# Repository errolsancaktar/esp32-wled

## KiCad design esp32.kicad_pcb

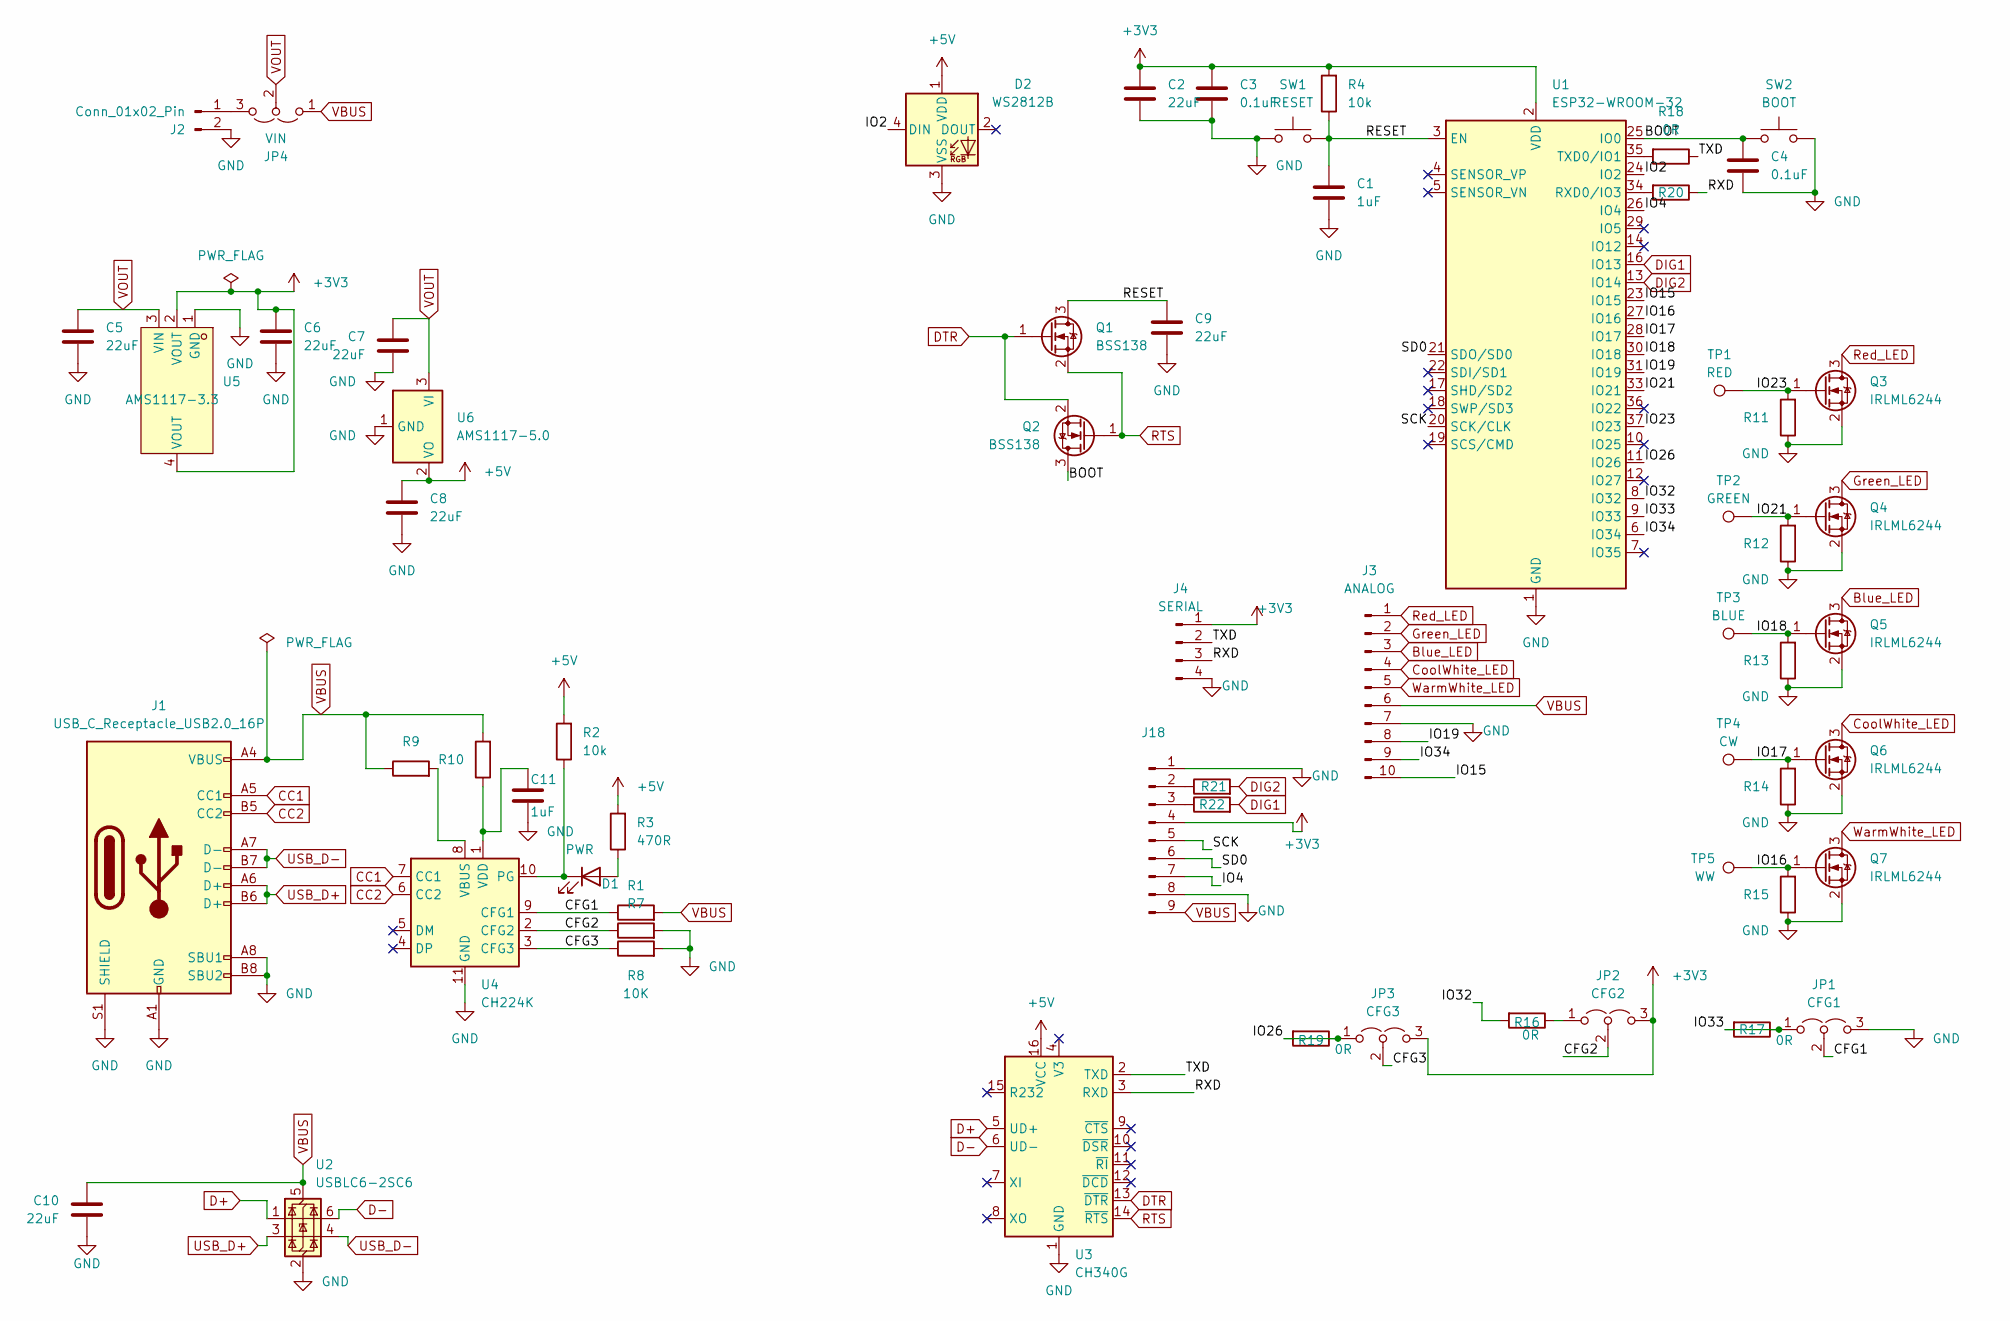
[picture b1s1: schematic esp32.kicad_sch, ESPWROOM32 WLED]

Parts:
C1, C11: 1uF; C_0805_2012Metric_Pad1.18x1.45mm_HandSolder
C2, C5, C6, C7, C8, C9, C10: 22uF; C_0805_2012Metric_Pad1.18x1.45mm_HandSolder
C3, C4: 0.1uF; C_0805_2012Metric_Pad1.18x1.45mm_HandSolder
D1: PWR; LED_0805_2012Metric_Pad1.15x1.40mm_HandSolder
D2: WS2812B; LED_WS2812B_PLCC4_5.0x5.0mm_P3.2mm
J1: USB_C_Receptacle_USB2.0_16P; USB_C_Receptacle_XKB_U262-16XN-4BVC11
J2: Conn_01x02_Pin; TerminalBlock_MaiXu_MX126-5.0-02P_1x02_P5.00mm
J3: ANALOG; PinHeader_1x10_P2.54mm_Vertical
J4: SERIAL; PinSocket_1x04_P2.54mm_Vertical
J18: Conn_01x09_Pin; PinSocket_1x09_P2.54mm_Vertical
JP1: CFG1; SolderJumper-3_P1.3mm_Open_RoundedPad1.0x1.5mm_NumberLabels
JP2: CFG2; SolderJumper-3_P1.3mm_Open_RoundedPad1.0x1.5mm_NumberLabels
JP3: CFG3; SolderJumper-3_P1.3mm_Open_RoundedPad1.0x1.5mm_NumberLabels
JP4: VIN; SolderJumper-3_P1.3mm_Open_RoundedPad1.0x1.5mm_NumberLabels
Q1, Q2: BSS138; SOT-23
Q3, Q4, Q5, Q6, Q7: IRLML6244; SOT-23
R1, R7, R8, R9, R10, R11, R12, R13, R14, R15: 10K; R_0805_2012Metric_Pad1.20x1.40mm_HandSolder
R2, R4: 10k; R_0805_2012Metric_Pad1.20x1.40mm_HandSolder
R3, R21, R22: 470R; R_0805_2012Metric_Pad1.20x1.40mm_HandSolder
R16, R17, R18, R19, R20: 0R; R_0805_2012Metric_Pad1.20x1.40mm_HandSolder
SW1: RESET; SW_SPST_SKQG_WithStem
SW2: BOOT; SW_SPST_SKQG_WithStem
TP1: RED; TestPoint_Pad_1.0x1.0mm
TP2: GREEN; TestPoint_Pad_1.0x1.0mm
TP3: BLUE; TestPoint_Pad_1.0x1.0mm
TP4: CW; TestPoint_Pad_1.0x1.0mm
TP5: WW; TestPoint_Pad_1.0x1.0mm
U1: ESP32-WROOM-32
U2: USBLC6-2SC6; SOT-23-6
U3: CH340G; SOIC-16_3.9x9.9mm_P1.27mm
U4: CH224K; SSOP-10-1EP_3.9x4.9mm_P1mm_EP2.1x3.3mm
U5: AMS1117-3.3; SOT-223-3_TabPin2; LCSC Part C6186
U6: AMS1117-5.0; SOT-223-3_TabPin2

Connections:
+3V3: C2.1, C3.1, C6.1, J4.1, J18.4, JP2.3 (B), JP3.3 (B), R4.2, U1.2 (VDD), U5.2 (VOUT), U5.4 (VOUT)
+5V: C8.1, D2.1 (VDD), R2.2, R3.2, U3.16 (VCC), U6.2 (VO)
/BOOT: C4.1, Q2.3 (D), SW2.1, U1.25 (IO0)
/CFG1: JP1.2 (C), R1.1, U4.9 (CFG1)
/CFG2: JP2.2 (C), R7.1, U4.2 (CFG2)
/CFG3: JP3.2 (C), R8.1, U4.3 (CFG3)
/IO2: D2.4 (DIN), U1.24 (IO2)
/IO4: J18.7, U1.26 (IO4)
/IO15: J3.10, U1.23 (IO15)
/IO16: Q7.1 (G), R15.2, TP5.1, U1.27 (IO16)
/IO17: Q6.1 (G), R14.2, TP4.1, U1.28 (IO17)
/IO18: Q5.1 (G), R13.2, TP3.1, U1.30 (IO18)
/IO19: J3.8, U1.31 (IO19)
/IO21: Q4.1 (G), R12.2, TP2.1, U1.33 (IO21)
/IO23: Q3.1 (G), R11.2, TP1.1, U1.37 (IO23)
/IO26: JP3.1 (A), R19.1, R19.2, U1.11 (IO26)
/IO32: R16.2, U1.8 (IO32)
/IO33: JP1.1 (A), R17.1, R17.2, U1.9 (IO33)
/IO34: J3.9, U1.6 (IO34)
/RESET: C1.1, C9.1, Q1.3 (D), R4.1, SW1.2, U1.3 (EN)
/RXD: J4.3, R20.1, U3.3 (RXD)
/SCK: J18.5, U1.20 (SCK/CLK)
/SD0: J18.6, U1.21 (SDO/SD0)
/TXD: J4.2, R18.1, U3.2 (TXD)
Blue_LED: J3.3, Q5.3 (D)
CC1: J1.A5 (CC1), U4.7 (CC1)
CC2: J1.B5 (CC2), U4.6 (CC2)
CoolWhite_LED: J3.4, Q6.3 (D)
D+: U2.1 (I/O1), U3.5 (UD+)
D-: U2.6 (I/O1), U3.6 (UD-)
DIG1: R22.2, U1.16 (IO13)
DIG2: R21.2, U1.13 (IO14)
DTR: Q1.1 (G), Q2.2 (S), U3.13 (~DTR)
GND: C1.2, C2.2, C3.2, C4.2, C5.2, C6.2, C7.2, C8.2, C9.2, C10.2, C11.2, D2.3 (VSS), J1.A1 (GND), J1.A8 (SBU1), J1.A12 (GND), J1.B1 (GND), J1.B8 (SBU2), J1.B12 (GND), J1.S1 (SHIELD), J2.2, J3.7, J4.4, J18.1, J18.8, JP1.3 (B), Q3.2 (S), Q4.2 (S), Q5.2 (S), Q6.2 (S), Q7.2 (S), R7.2, R8.2, R11.1, R12.1, R13.1, R14.1, R15.1, SW1.1, SW2.2, U1.1 (GND), U1.15 (GND), U1.38 (GND), U1.39 (GND), U2.2 (GND), U3.1 (GND), U4.11 (GND), U5.1 (GND), U6.1 (GND)
Green_LED: J3.2, Q4.3 (D)
unnamed: D1.2 (A), R3.1
unnamed: D1.1 (K), R2.1, U4.10 (PG)
unnamed: J2.1, JP4.3 (B)
unnamed: J18.2, R21.1
unnamed: J18.3, R22.1
unnamed: JP2.1 (A), R16.1
unnamed: R20.2, U1.34 (RXD0/IO3)
unnamed: R18.2, U1.35 (TXD0/IO1)
unnamed: R9.2, U4.8 (VBUS)
unnamed: C11.1, R10.1, U4.1 (VDD)
RTS: Q1.2 (S), Q2.1 (G), U3.14 (~RTS)
Red_LED: J3.1, Q3.3 (D)
USB_D+: J1.A6 (D+), J1.B6 (D+), U2.3 (I/O2)
USB_D-: J1.A7 (D-), J1.B7 (D-), U2.4 (I/O2)
VBUS: C10.1, J1.A4 (VBUS), J1.A9 (VBUS), J1.B4 (VBUS), J1.B9 (VBUS), J3.6, J18.9, JP4.1 (A), R1.2, R9.1, R10.2, U2.5 (VBUS)
VOUT: C5.1, C7.1, JP4.2 (C), U5.3 (VIN), U6.3 (VI)
WarmWhite_LED: J3.5, Q7.3 (D)

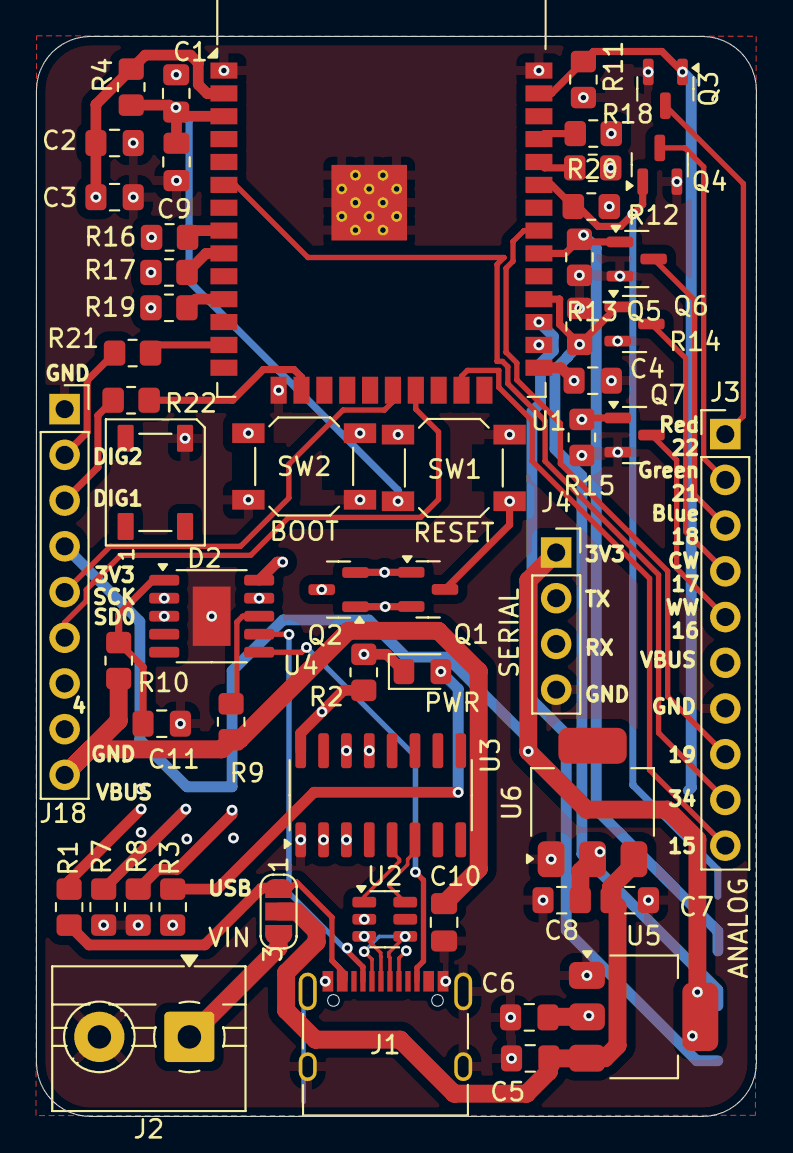
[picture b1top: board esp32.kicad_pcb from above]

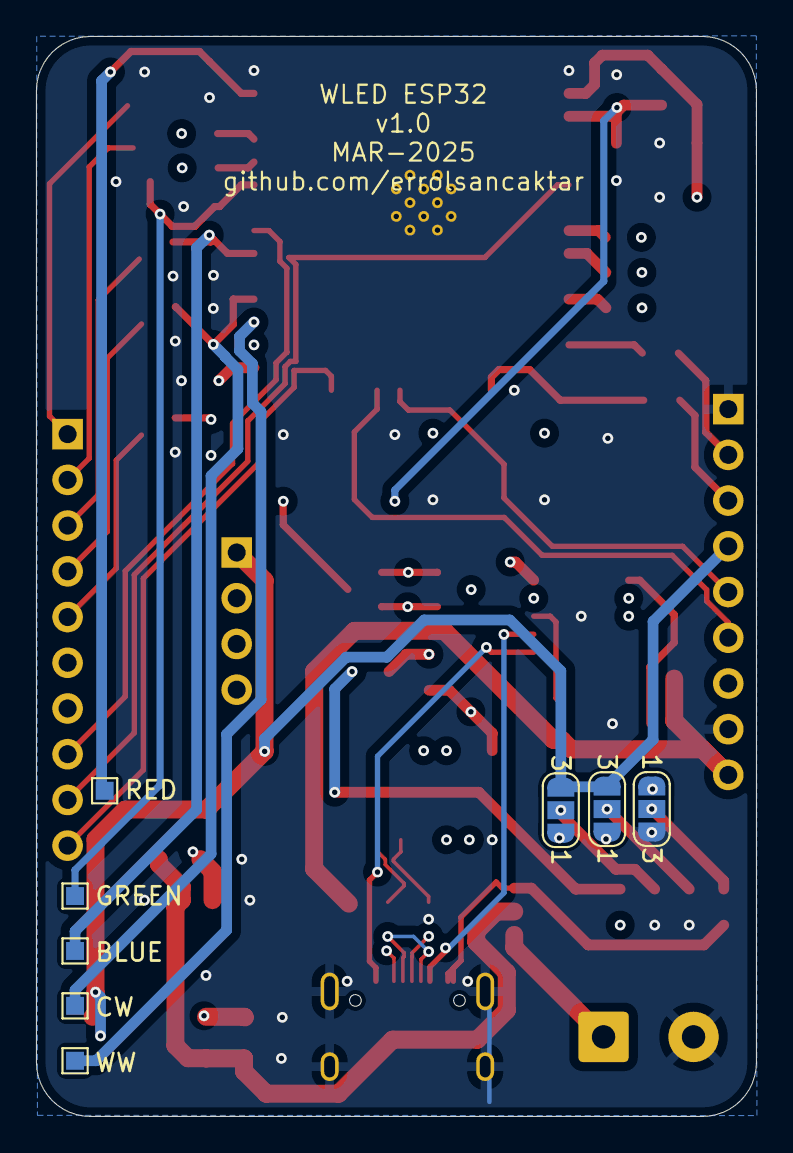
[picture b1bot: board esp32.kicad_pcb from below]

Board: 4 copper layers, 40.0 x 60.0 mm, 62 parts (8 on the bottom side), 52 nets.

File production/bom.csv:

Designator,Footprint,Quantity,Value,LCSC Part #
"C1, C11",0805,2,1uF,
"C10, C2, C5, C6, C7, C8, C9",0805,7,22uF,
"C3, C4",0805,2,0.1uF,
D1,0805,1,PWR,
D2,LED_WS2812B_PLCC4_5.0x5.0mm_P3.2mm,1,WS2812B,
J1,USB_C_Receptacle_XKB_U262-16XN-4BVC11,1,USB_C_Receptacle_USB2.0_16P,
J18,PinSocket_1x09_P2.54mm_Vertical,1,Conn_01x09_Pin,
J2,TerminalBlock_MaiXu_MX126-5.0-02P_1x02_P5.00mm,1,Conn_01x02_Pin,
J3,PinHeader_1x10_P2.54mm_Vertical,1,ANALOG,
J4,PinSocket_1x04_P2.54mm_Vertical,1,SERIAL,
"Q1, Q2",SOT-23,2,BSS138,
"Q3, Q4, Q5, Q6, Q7",SOT-23,5,IRLML6244,
"R1, R10, R11, R12, R13, R14, R15, R2, R4, R7, R8, R9",0805,12,10K,
"R16, R17, R18, R19, R20",0805,5,0R,
"R21, R22, R3",0805,3,470R,
SW1,SW_SPST_SKQG_WithStem,1,RESET,
SW2,SW_SPST_SKQG_WithStem,1,BOOT,
TP1,TestPoint_Pad_1.0x1.0mm,1,RED,
TP2,TestPoint_Pad_1.0x1.0mm,1,GREEN,
TP3,TestPoint_Pad_1.0x1.0mm,1,BLUE,
TP4,TestPoint_Pad_1.0x1.0mm,1,CW,
TP5,TestPoint_Pad_1.0x1.0mm,1,WW,
U1,ESP32-WROOM-32,1,ESP32-WROOM-32,
U2,SOT-23-6,1,USBLC6-2SC6,
U3,SOIC-16_3.9x9.9mm_P1.27mm,1,CH340G,
U4,SSOP-10-1EP_3.9x4.9mm_P1mm_EP2.1x3.3mm,1,CH224K,
U5,SOT-223,1,AMS1117-3.3,C6186
U6,SOT-223,1,AMS1117-5.0,

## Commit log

2025-04-11 init v2
